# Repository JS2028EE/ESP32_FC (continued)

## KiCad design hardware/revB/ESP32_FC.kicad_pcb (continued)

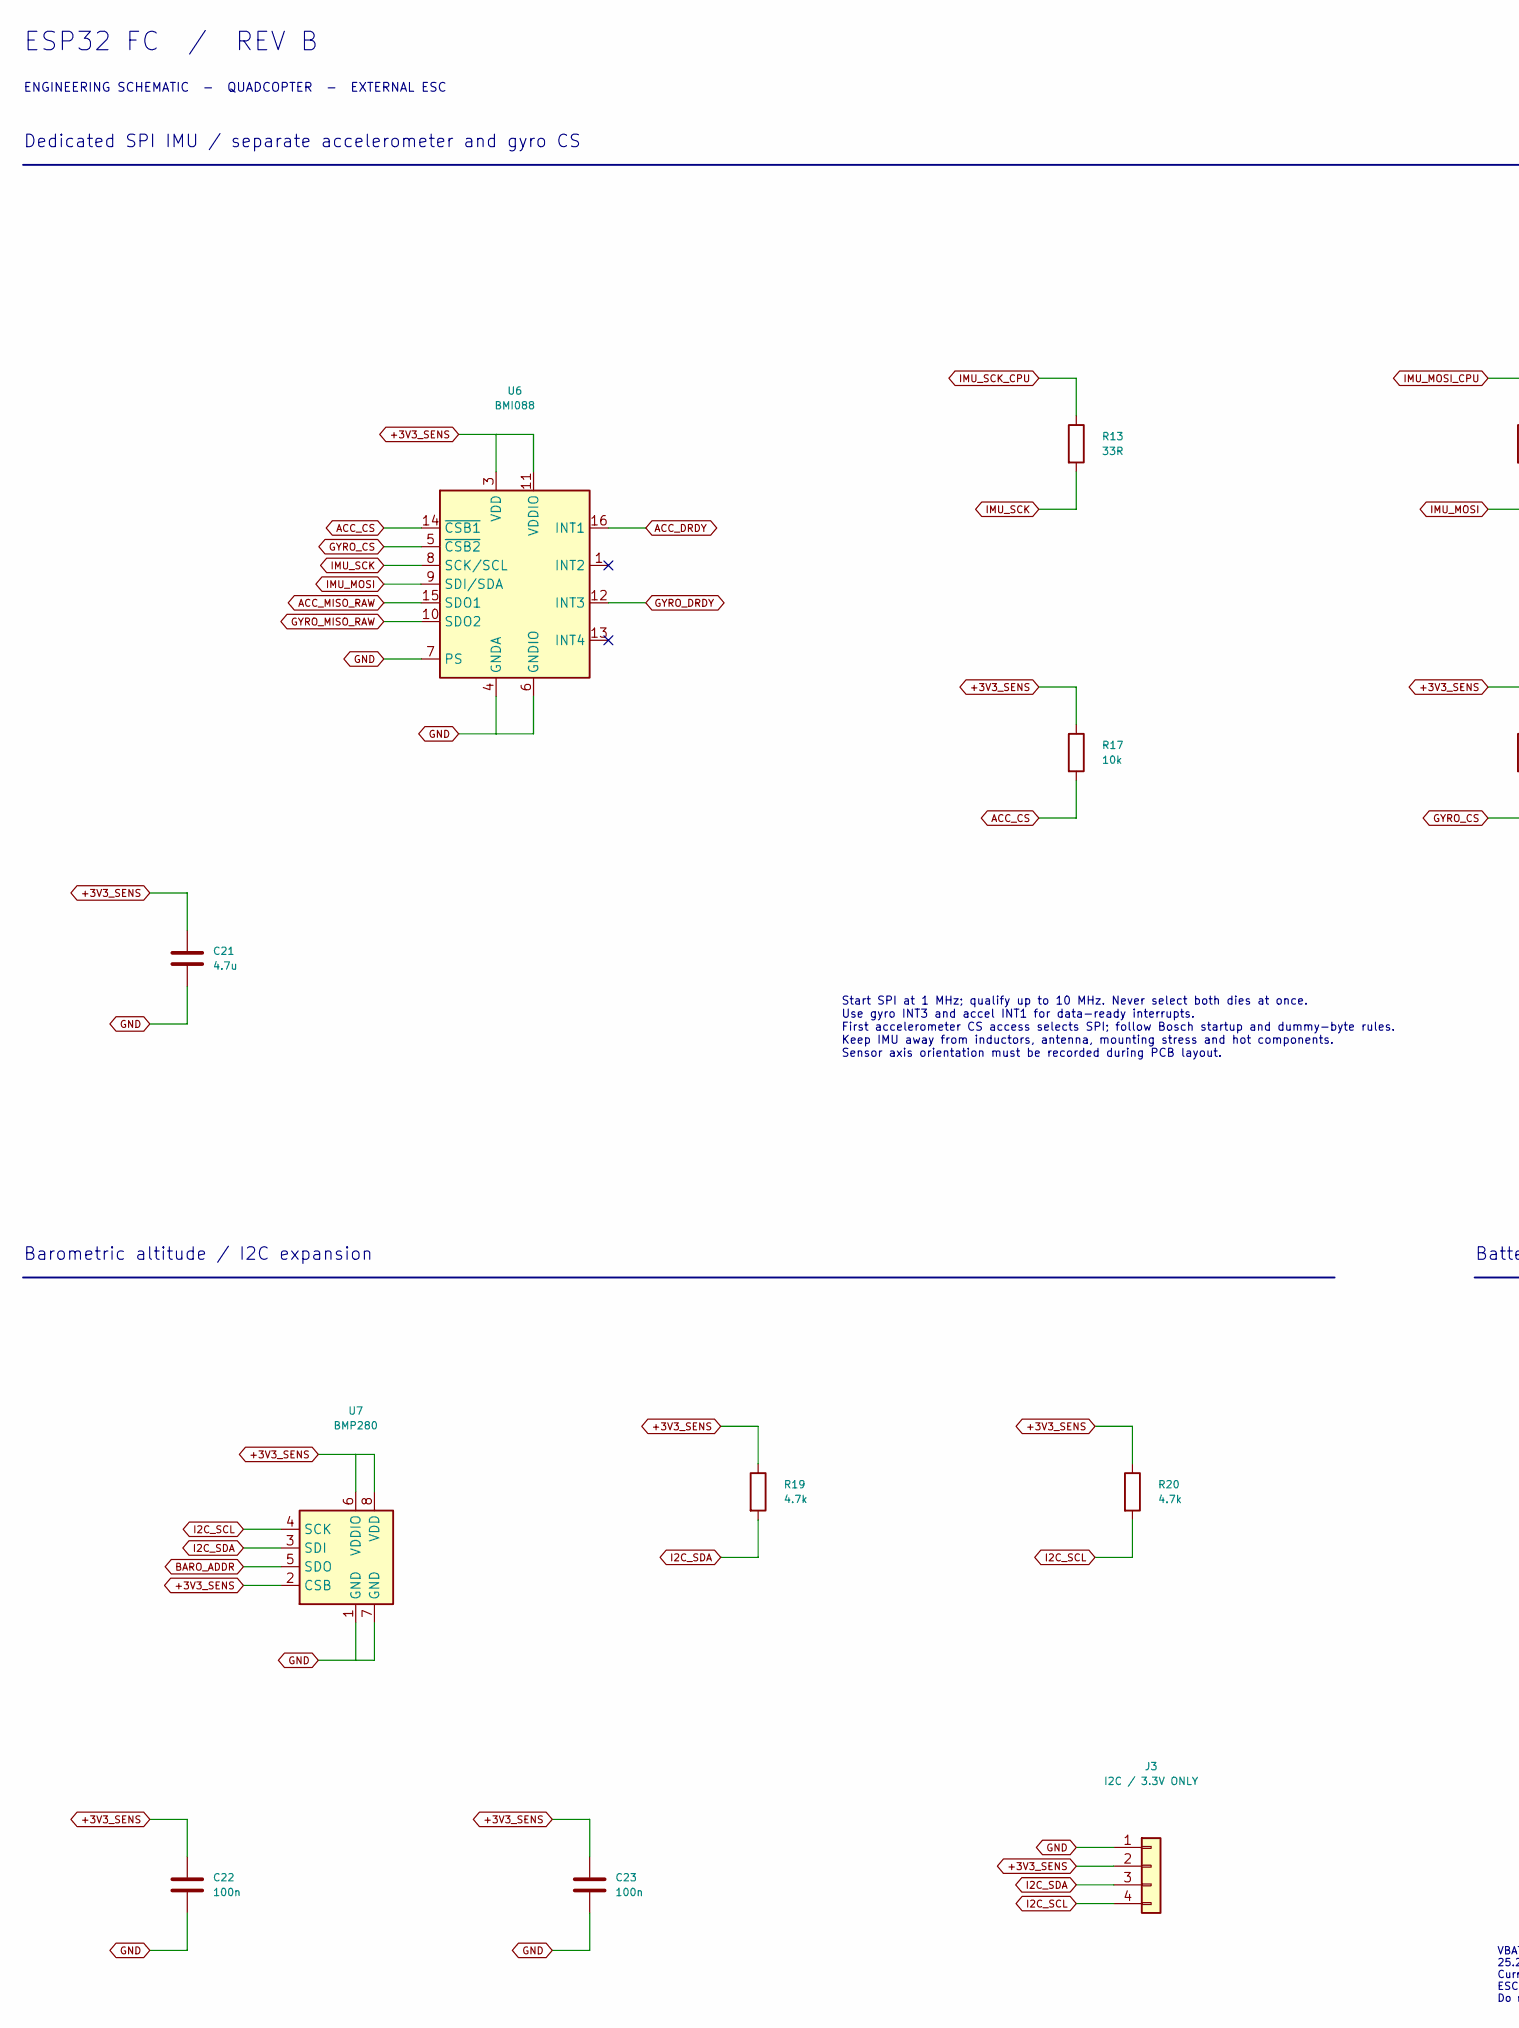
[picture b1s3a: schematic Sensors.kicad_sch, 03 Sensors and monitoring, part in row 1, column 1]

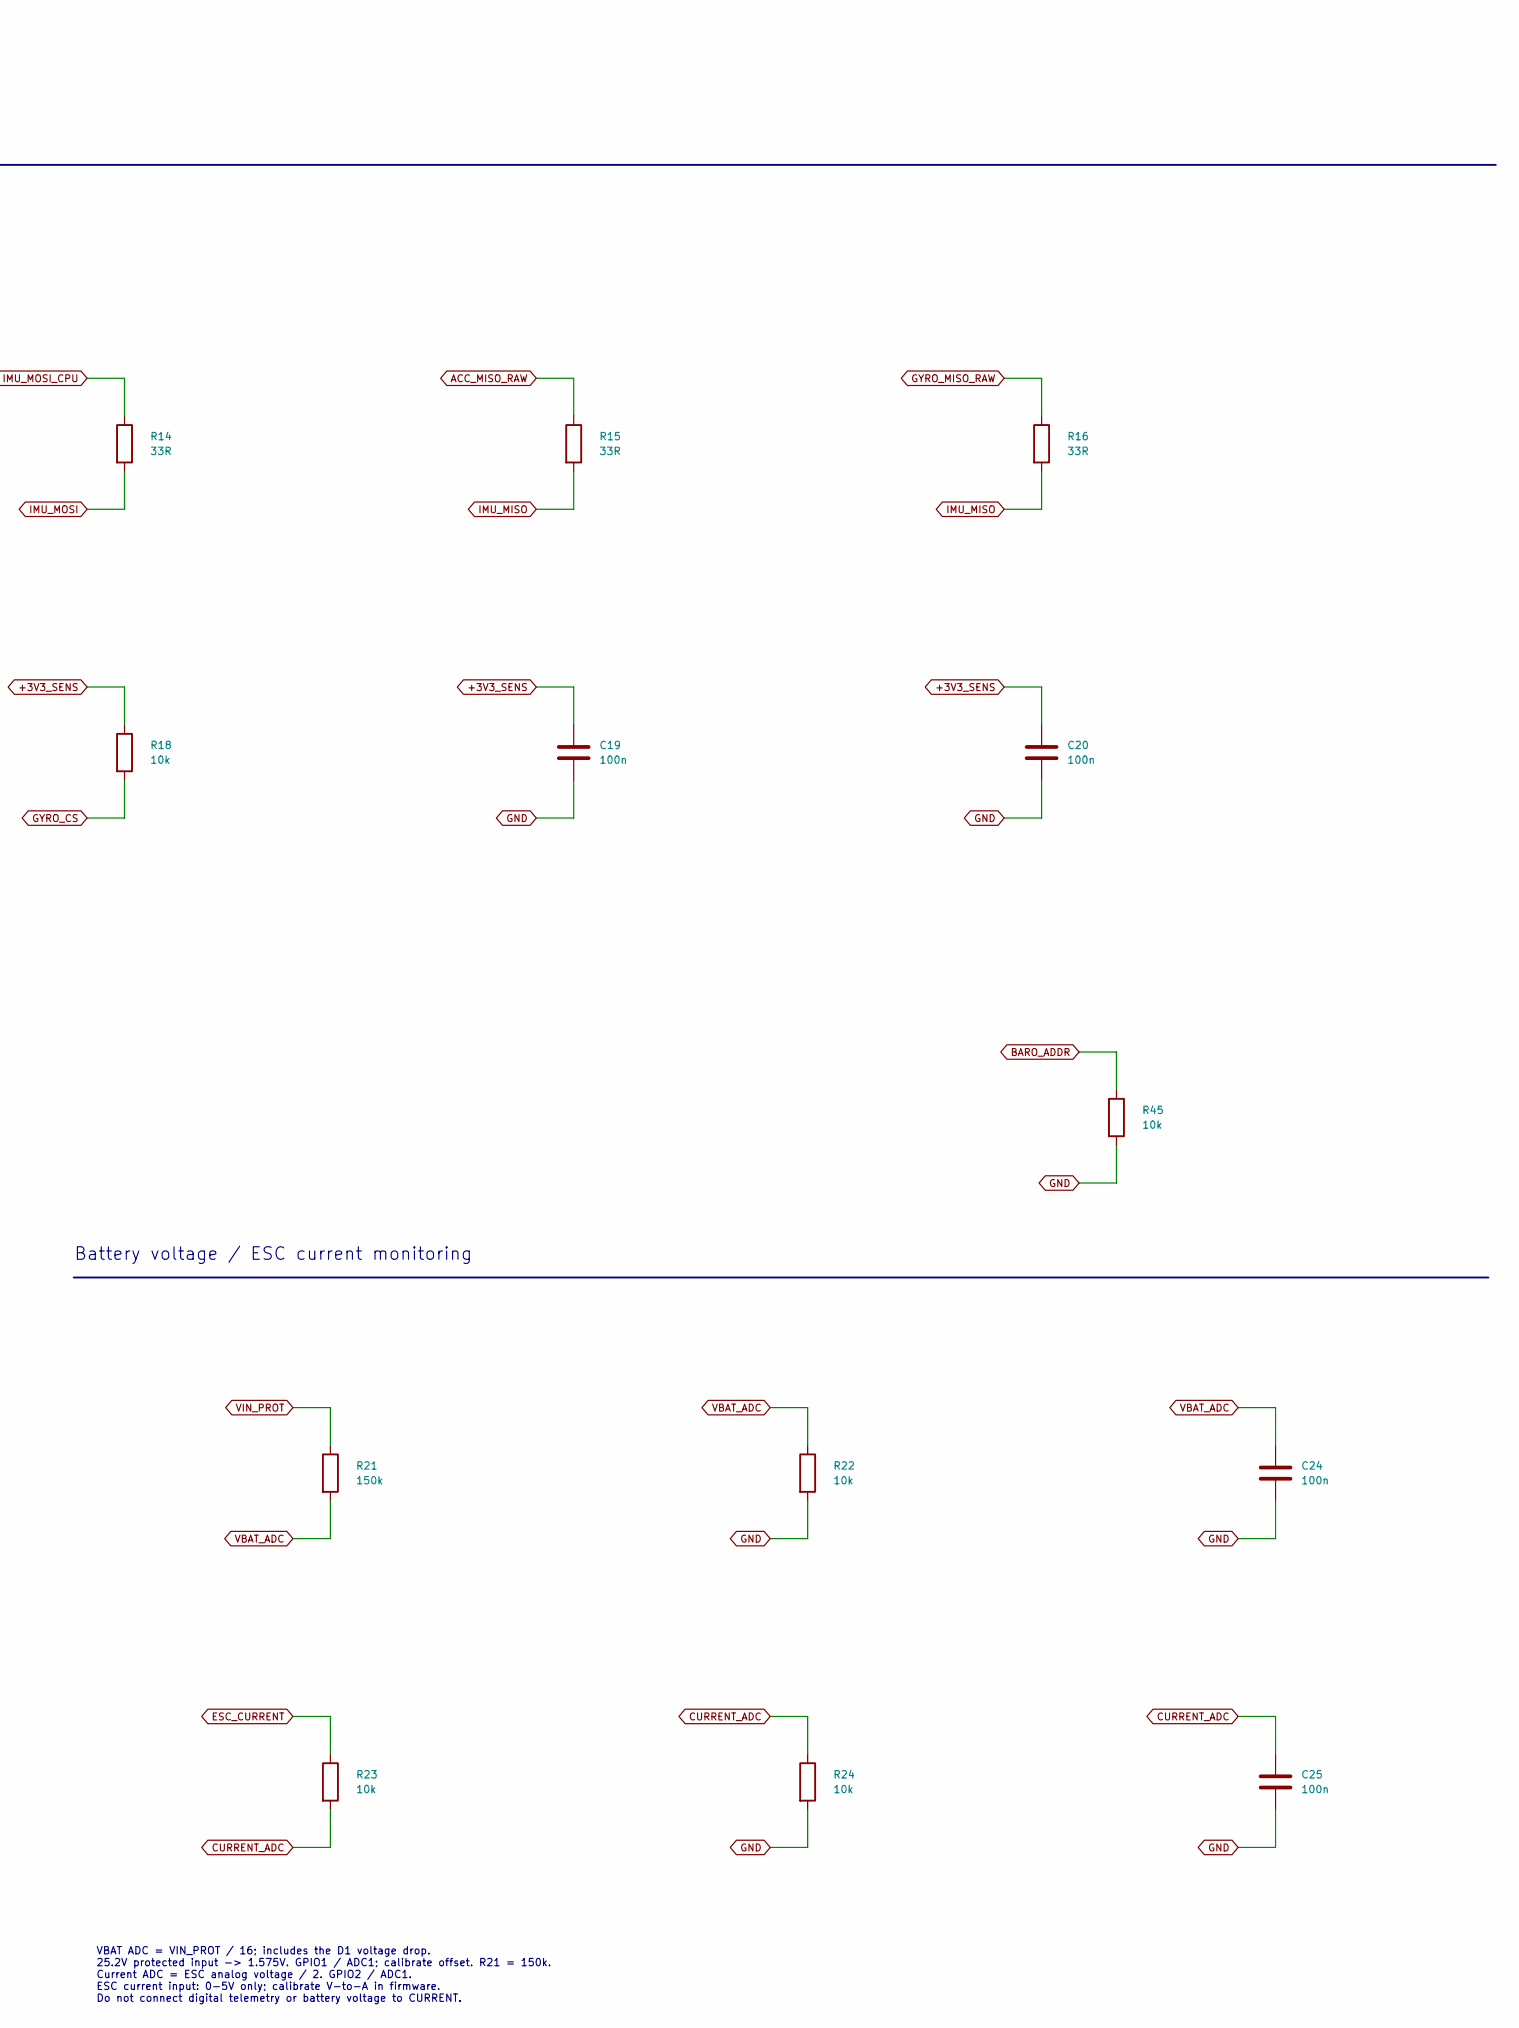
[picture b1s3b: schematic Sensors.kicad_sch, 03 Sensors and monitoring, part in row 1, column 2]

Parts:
C19, C20, C22, C23, C24, C25: 100n; C_0603_1608Metric; MPN GRM188R71C104KA01D
C21: 4.7u; C_0603_1608Metric; MPN GRM188R61C475KE11D
J3: I2C / 3.3V ONLY; PinHeader_1x04_P2.54mm_Vertical; MPN TSW-104-07-G-S
R13, R14, R15, R16: 33R; R_0603_1608Metric; MPN RC0603FR-0733RL
R17, R18, R23, R24, R45: 10k; R_0603_1608Metric; MPN RC0603FR-0710KL
R19, R20: 4.7k; R_0603_1608Metric; MPN RC0603FR-074K7L
R21: 150k; R_0603_1608Metric; MPN RT0603BRD07150KL
R22: 10k; R_0603_1608Metric; MPN RT0603BRD0710KL
U6: BMI088; Bosch_LGA-16_4.5x3mm_P0.5mm_LayoutBorder7x1y_ClockwisePinNu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; MPN BMI088
U7: BMP280; BMP280_SilkClear; MPN BMP280

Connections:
+3V3_SENS: C19.1, C20.1, C21.1, C22.1, C23.1, J3.2, R17.1, R18.1, R19.1, R20.1, U6.3 (VDD), U6.11 (VDDIO), U7.2 (CSB), U7.6 (VDDIO), U7.8 (VDD); also elsewhere on the board
ACC_CS: R17.2, U6.14 (~CSB1); also elsewhere on the board
ACC_DRDY: U6.16 (INT1); also elsewhere on the board
ACC_MISO_RAW: R15.1, U6.15 (SDO1)
BARO_ADDR: R45.1, U7.5 (SDO)
CURRENT_ADC: C25.1, R23.2, R24.1; also elsewhere on the board
ESC_CURRENT: R23.1; also elsewhere on the board
GND: C19.2, C20.2, C21.2, C22.2, C23.2, C24.2, C25.2, J3.1, R22.2, R24.2, R45.2, U6.2 (GNDA), U6.4 (GNDA), U6.6 (GNDIO), U6.7 (PS), U7.1 (GND), U7.7 (GND); also elsewhere on the board
GYRO_CS: R18.2, U6.5 (~CSB2); also elsewhere on the board
GYRO_DRDY: U6.12 (INT3); also elsewhere on the board
GYRO_MISO_RAW: R16.1, U6.10 (SDO2)
I2C_SCL: J3.4, R20.2, U7.4 (SCK); also elsewhere on the board
I2C_SDA: J3.3, R19.2, U7.3 (SDI); also elsewhere on the board
IMU_MISO: R15.2, R16.2; also elsewhere on the board
IMU_MOSI: R14.2, U6.9 (SDI/SDA)
IMU_MOSI_CPU: R14.1; also elsewhere on the board
IMU_SCK: R13.2, U6.8 (SCK/SCL)
IMU_SCK_CPU: R13.1; also elsewhere on the board
VBAT_ADC: C24.1, R21.2, R22.1; also elsewhere on the board
VIN_PROT: R21.1; also elsewhere on the board

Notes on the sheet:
ESP32 FC / REV B
ENGINEERING SCHEMATIC - QUADCOPTER - EXTERNAL ESC
Dedicated SPI IMU / separate accelerometer and gyro CS
Start SPI at 1 MHz; qualify up to 10 MHz. Never select both dies at once. Use gyro INT3 and accel INT1 for data-ready interrupts. First accelerometer CS access selects SPI; follow Bosch startup and dummy-byte rules. Keep IMU away from inductors, antenna, mounting stress and hot components. Sensor a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
Barometric altitude / I2C expansion
Battery voltage / ESC current monitoring
VBAT ADC = VIN_PROT / 16; includes the D1 voltage drop. 25.2V protected input -> 1.575V. GPIO1 / ADC1; calibrate offset. R21 = 150k. Current ADC = ESC analog voltage / 2. GPIO2 / ADC1. ESC current input: 0-5V only; calibrate V-to-A in firmware. Do not connect digital telemetry or battery voltage to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

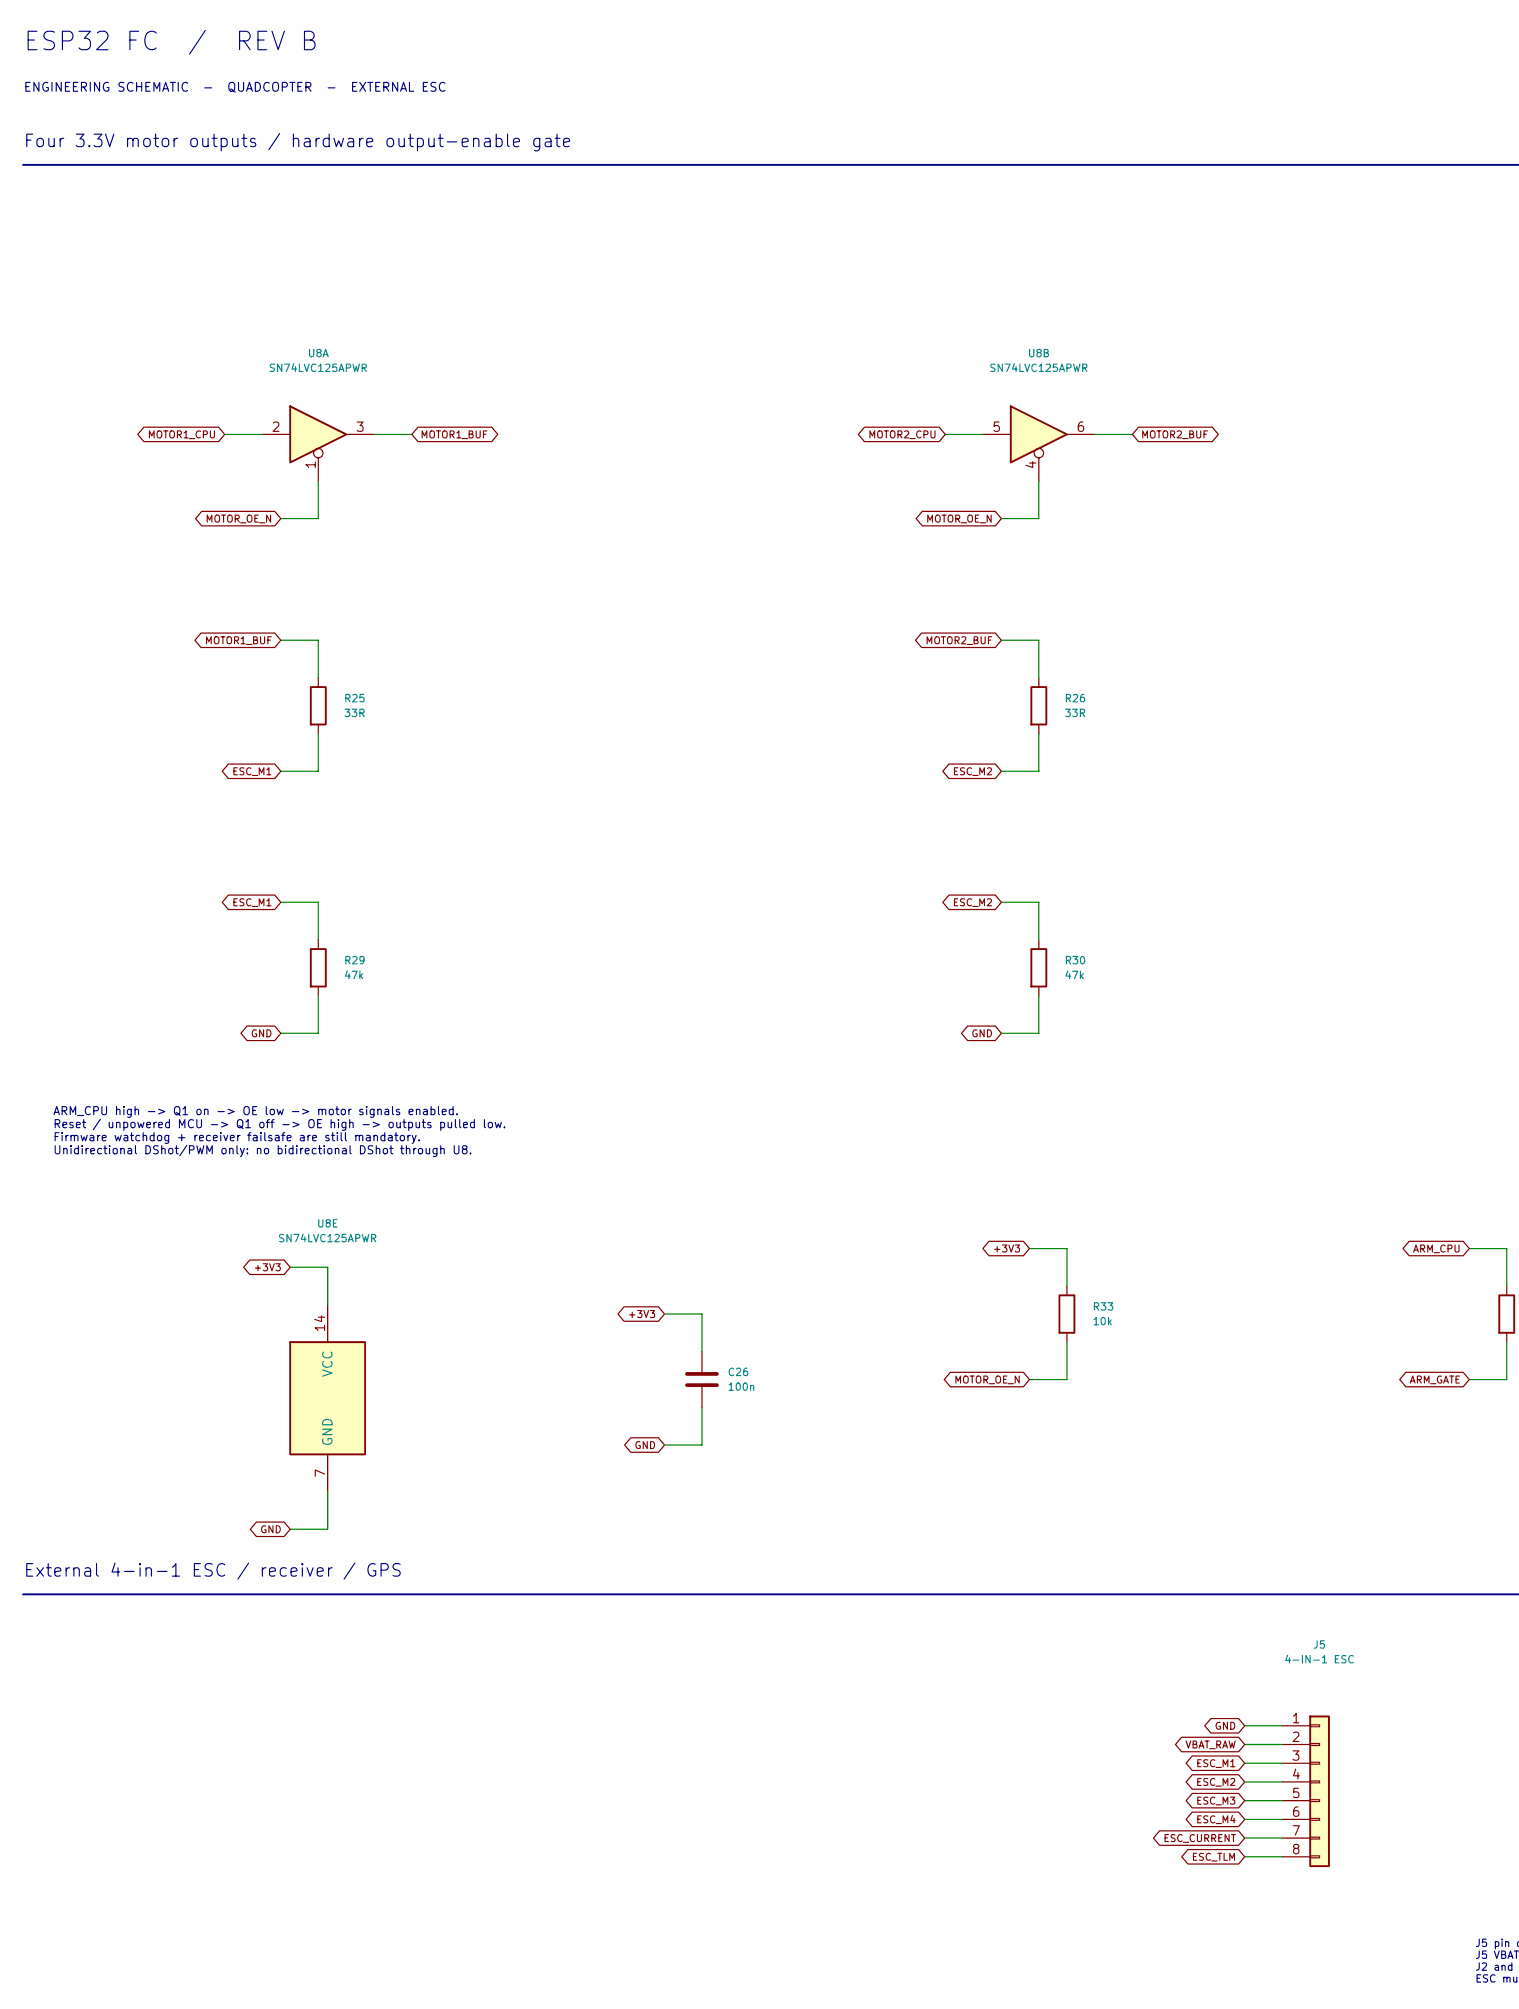
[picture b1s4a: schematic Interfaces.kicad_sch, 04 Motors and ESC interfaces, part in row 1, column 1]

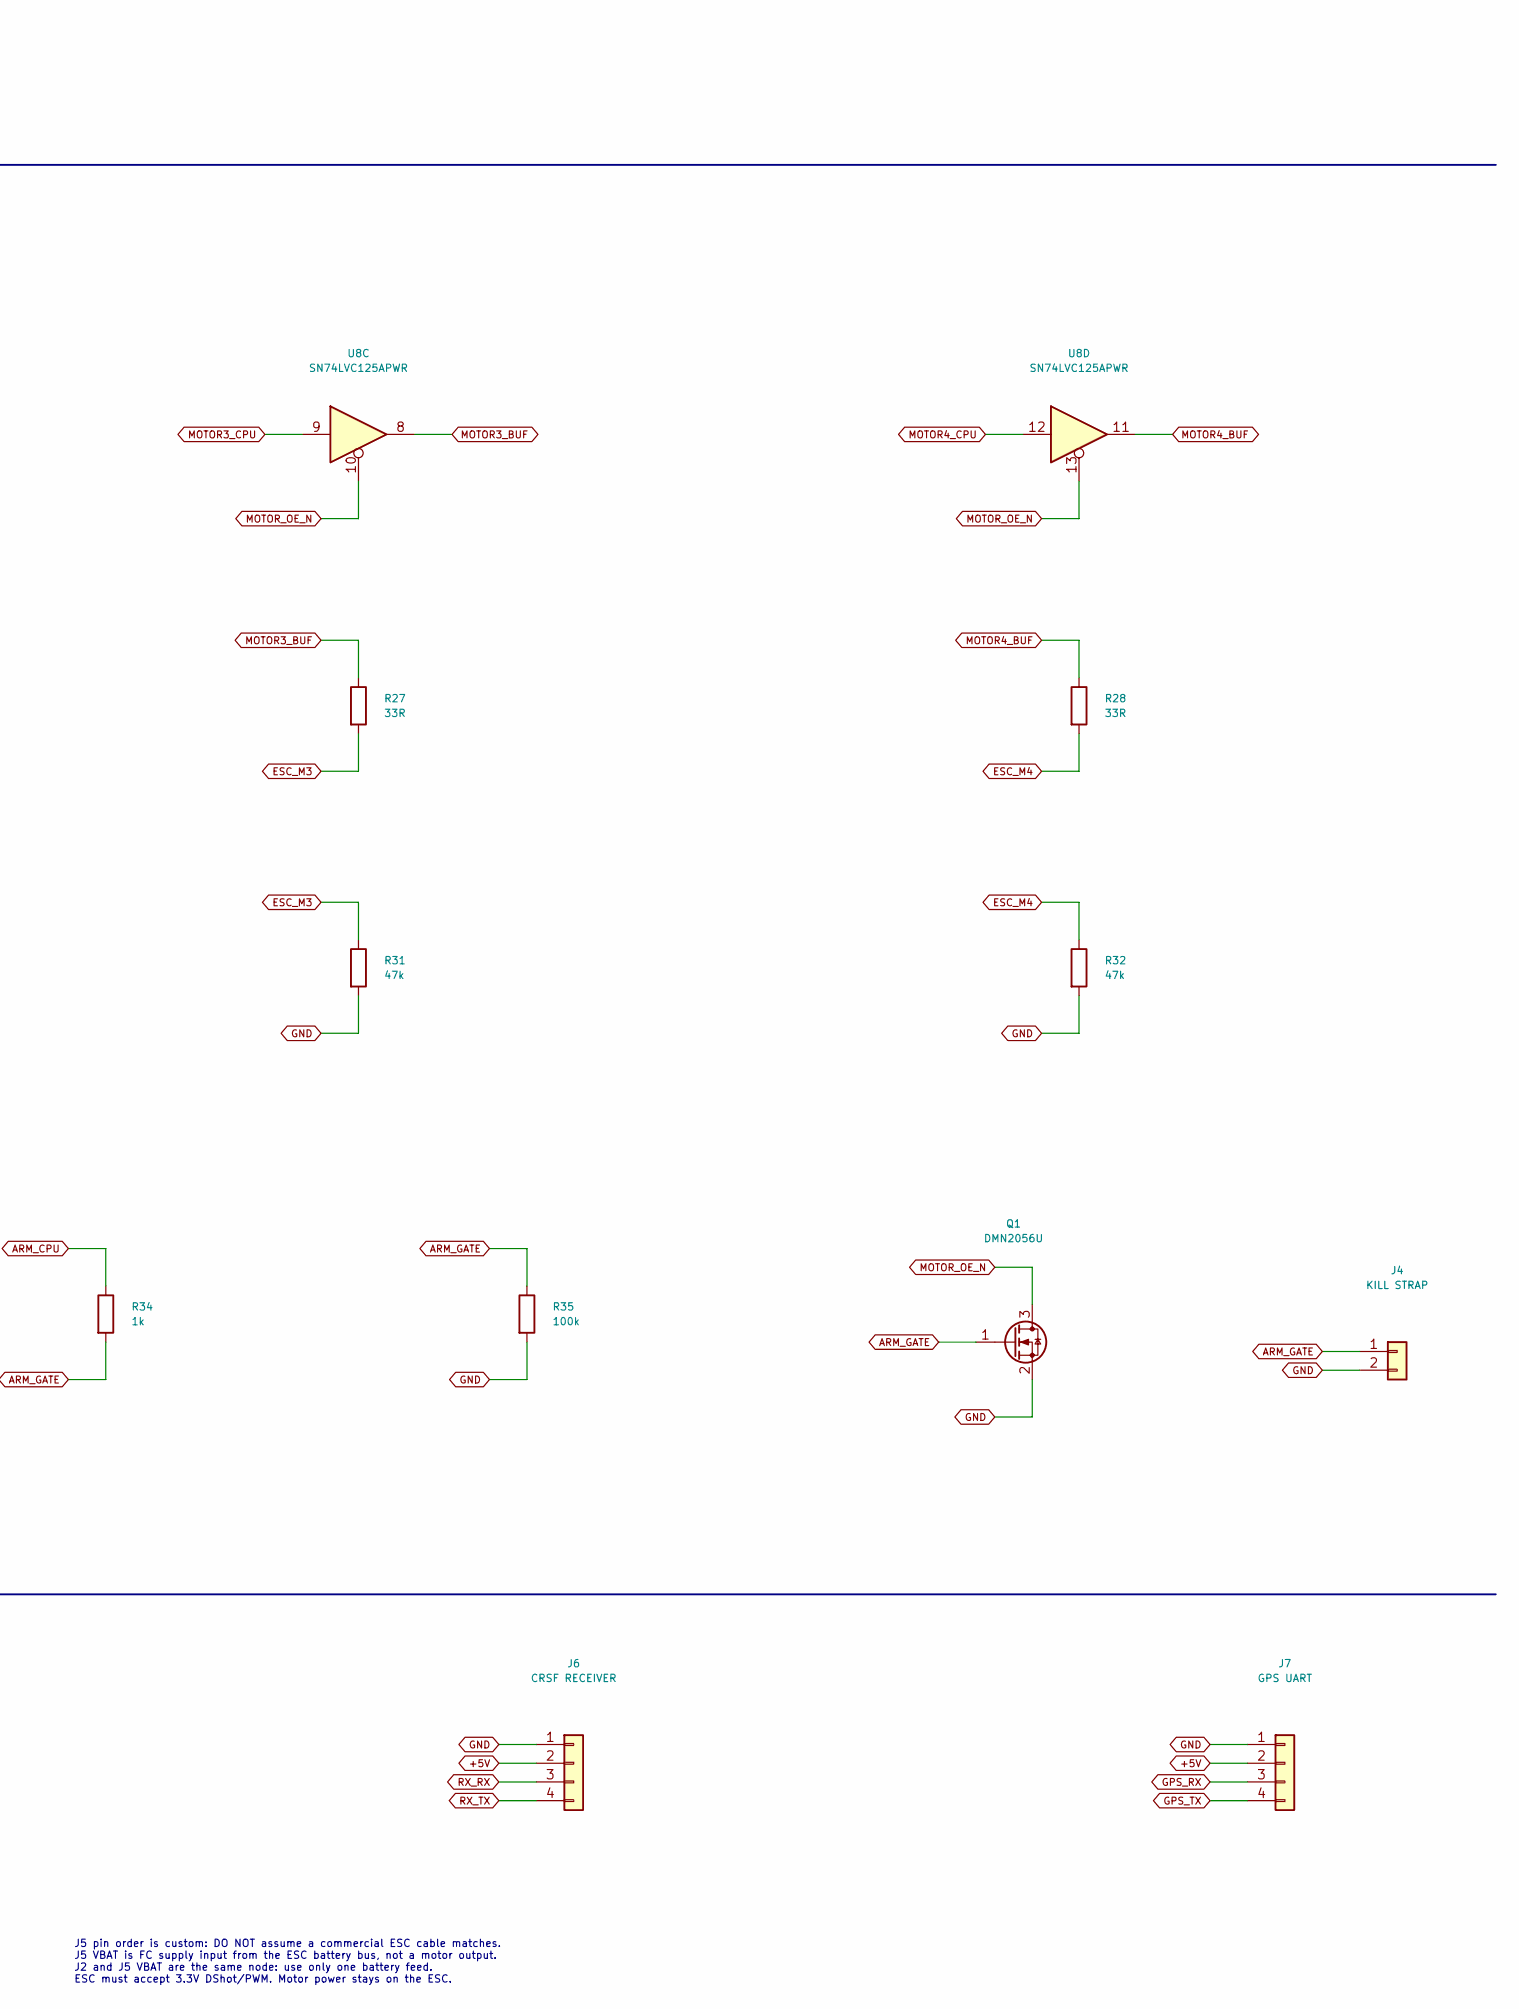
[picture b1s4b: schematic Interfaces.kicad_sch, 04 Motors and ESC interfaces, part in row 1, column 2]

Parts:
C26: 100n; C_0603_1608Metric; MPN GRM188R71C104KA01D
J4: KILL STRAP; PinHeader_1x02_P2.54mm_Vertical; MPN TSW-102-07-G-S
J5: 4-IN-1 ESC; PinHeader_1x08_P2.54mm_Vertical; MPN TSW-108-07-G-S
J6: CRSF RECEIVER; PinHeader_1x04_P2.54mm_Vertical; MPN TSW-104-07-G-S
J7: GPS UART; PinHeader_1x04_P2.54mm_Vertical; MPN TSW-104-07-G-S
Q1: DMN2056U; SOT-23; MPN DMN2056U-7
R25, R26, R27, R28: 33R; R_0603_1608Metric; MPN RC0603FR-0733RL
R29, R30, R31, R32: 47k; R_0603_1608Metric; MPN RC0603FR-0747KL
R33: 10k; R_0603_1608Metric; MPN RC0603FR-0710KL
R34: 1k; R_0603_1608Metric; MPN RC0603FR-071KL
R35: 100k; R_0603_1608Metric; MPN RC0603FR-07100KL
U8: SN74LVC125APWR; TSSOP-14_4.4x5mm_P0.65mm; MPN SN74LVC125APWR

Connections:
+3V3: C26.1, R33.1, U8.14 (VCC); also elsewhere on the board
+5V: J6.2, J7.2; also elsewhere on the board
ARM_CPU: R34.1; also elsewhere on the board
ARM_GATE: J4.1, Q1.1 (G), R34.2, R35.1
ESC_CURRENT: J5.7; also elsewhere on the board
ESC_M1: J5.3, R25.2, R29.1
ESC_M2: J5.4, R26.2, R30.1
ESC_M3: J5.5, R27.2, R31.1
ESC_M4: J5.6, R28.2, R32.1
ESC_TLM: J5.8; also elsewhere on the board
GND: C26.2, J4.2, J5.1, J6.1, J7.1, Q1.2 (S), R29.2, R30.2, R31.2, R32.2, R35.2, U8.7 (GND); also elsewhere on the board
GPS_RX: J7.3; also elsewhere on the board
GPS_TX: J7.4; also elsewhere on the board
MOTOR1_BUF: R25.1, U8.3
MOTOR1_CPU: U8.2; also elsewhere on the board
MOTOR2_BUF: R26.1, U8.6
MOTOR2_CPU: U8.5; also elsewhere on the board
MOTOR3_BUF: R27.1, U8.8
MOTOR3_CPU: U8.9; also elsewhere on the board
MOTOR4_BUF: R28.1, U8.11
MOTOR4_CPU: U8.12; also elsewhere on the board
MOTOR_OE_N: Q1.3 (D), R33.2, U8.1, U8.4, U8.10, U8.13
RX_RX: J6.3; also elsewhere on the board
RX_TX: J6.4; also elsewhere on the board
VBAT_RAW: J5.2; also elsewhere on the board

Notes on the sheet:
ESP32 FC / REV B
ENGINEERING SCHEMATIC - QUADCOPTER - EXTERNAL ESC
Four 3.3V motor outputs / hardware output-enable gate
ARM_CPU high -> Q1 on -> OE low -> motor signals enabled. Reset / unpowered MCU -> Q1 off -> OE high -> outputs pulled low. Firmware watchdog + receiver failsafe are still mandatory. Unidirectional DShot/PWM only: no bidirectional DShot through U8.
External 4-in-1 ESC / receiver / GPS
J5 pin order is custom: DO NOT assume a commercial ESC cable matches. J5 VBAT is FC supply input from the ESC battery bus, not a motor output. J2 and J5 VBAT are the same node: use only one battery feed. ESC must accept 3.3V DShot/PWM. Motor power stays on the ESC.

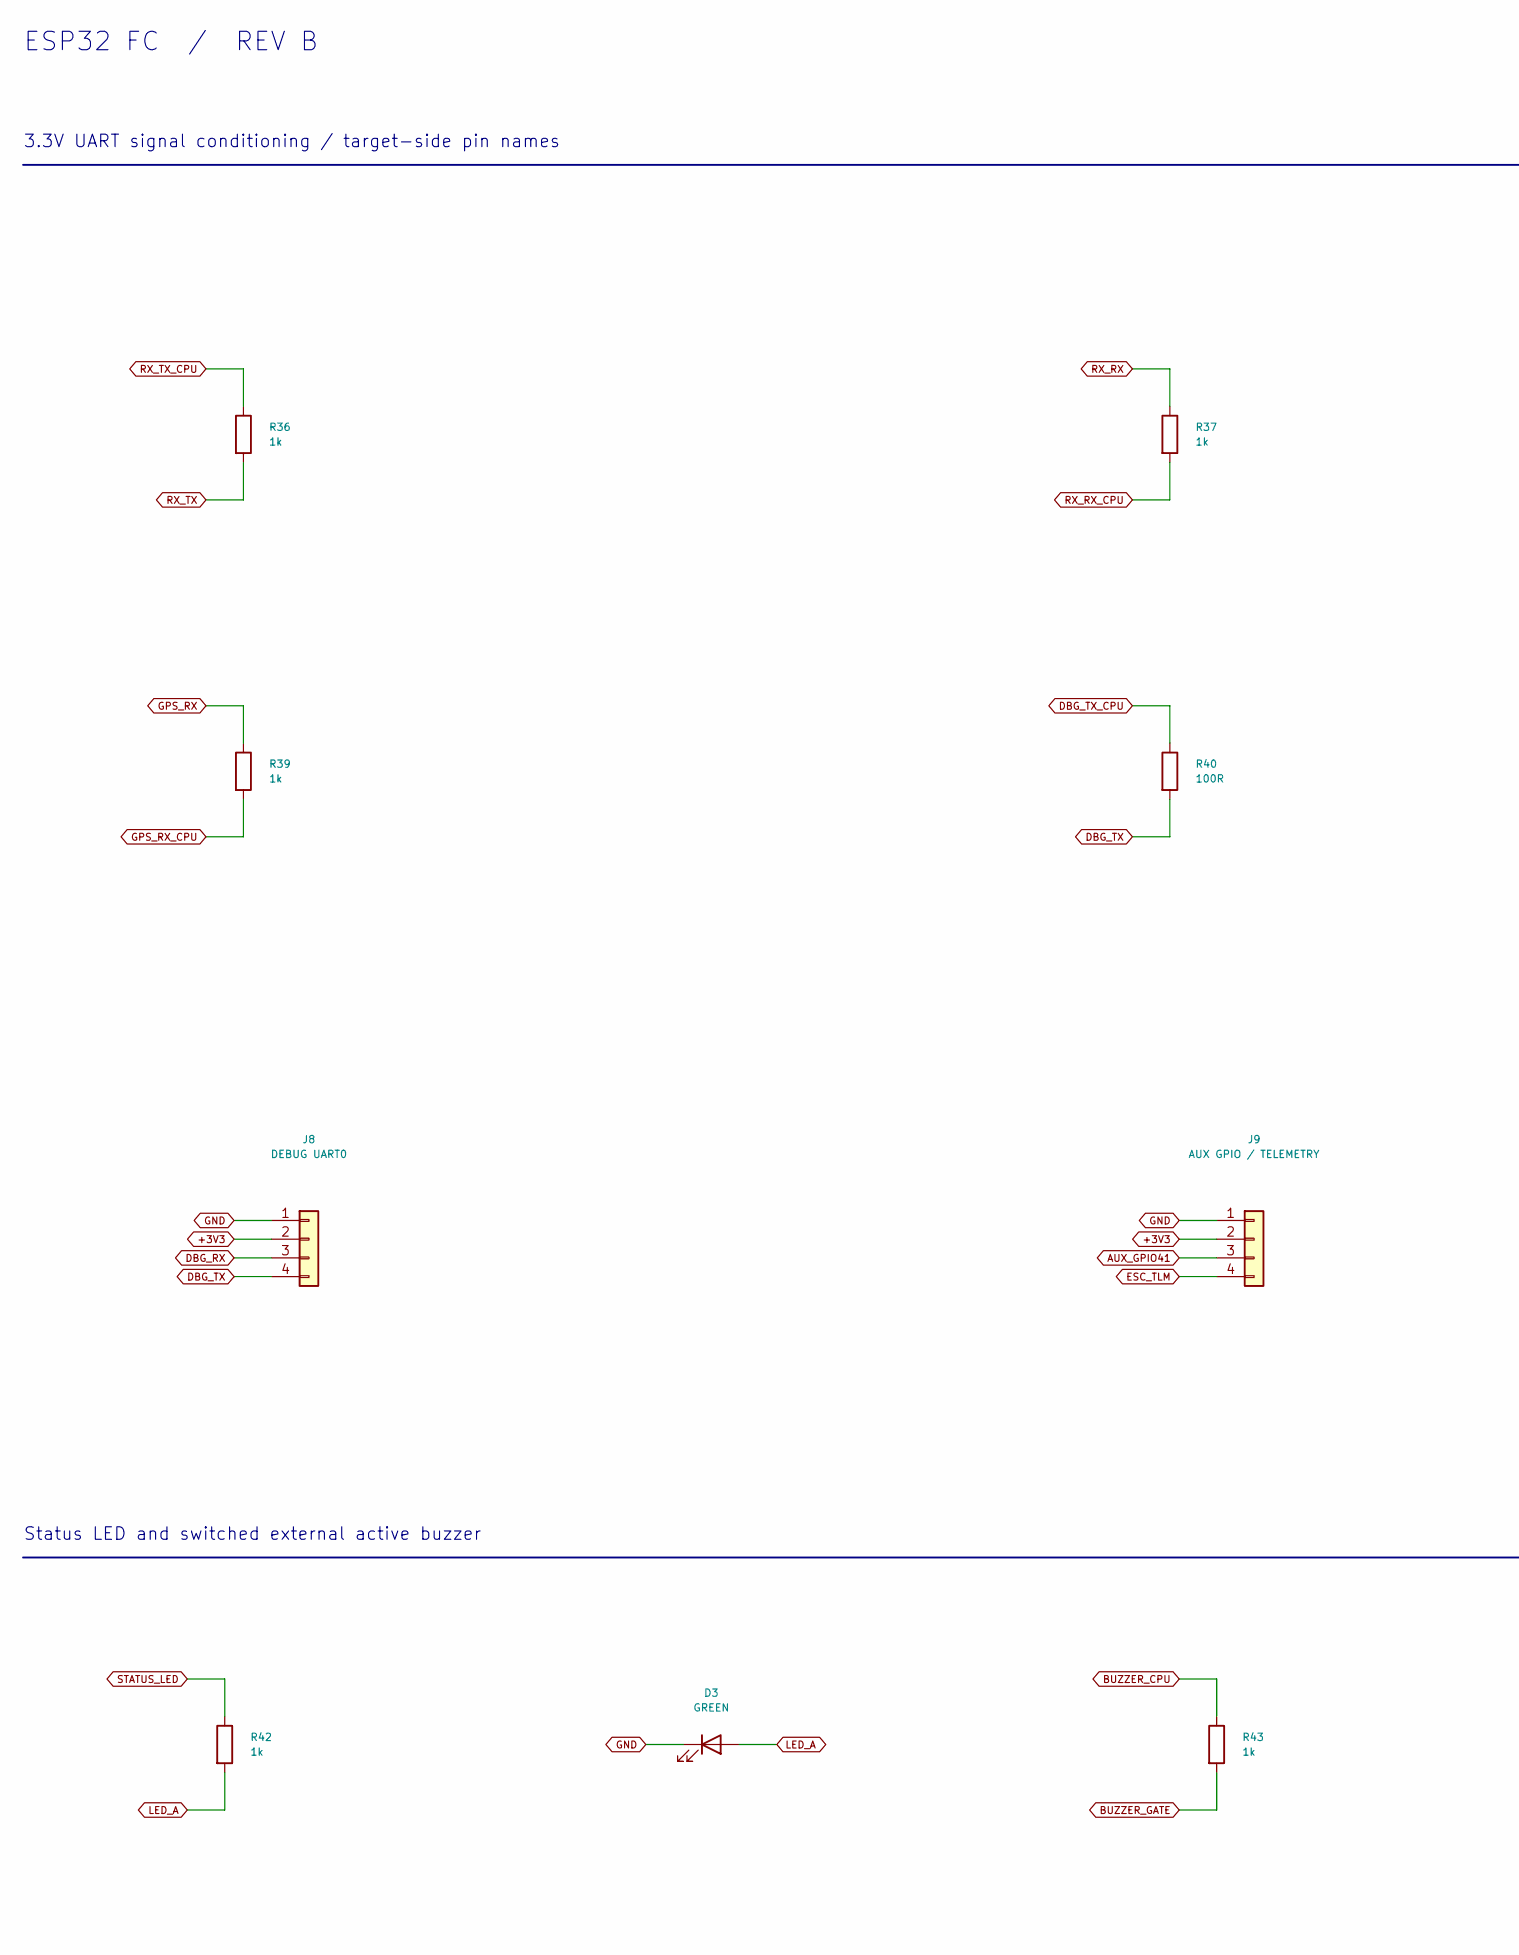
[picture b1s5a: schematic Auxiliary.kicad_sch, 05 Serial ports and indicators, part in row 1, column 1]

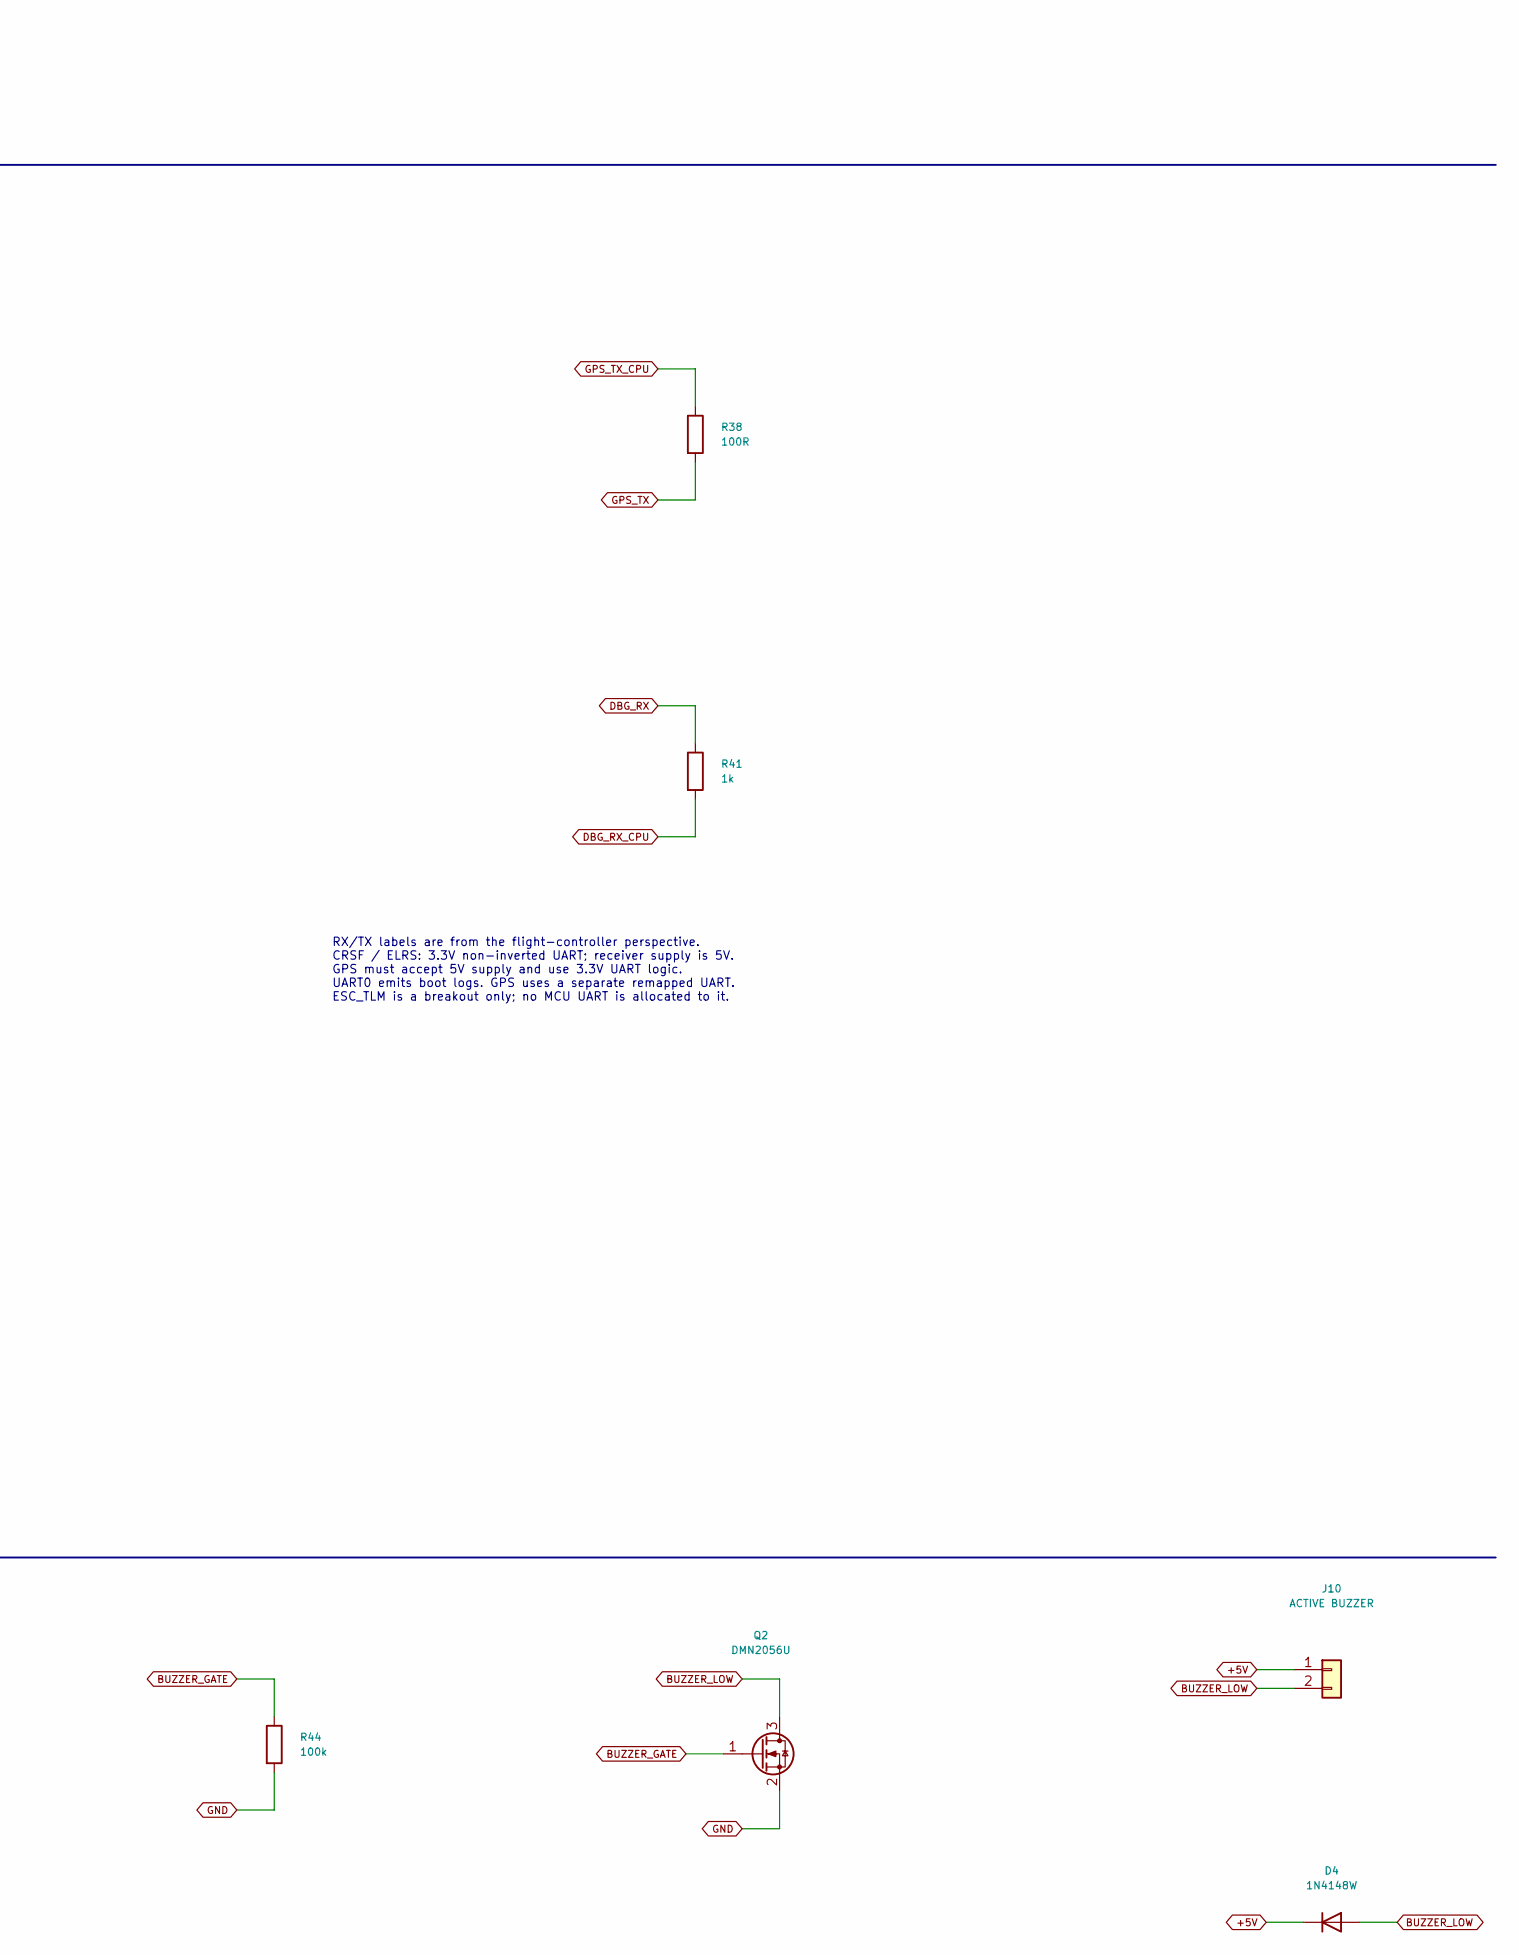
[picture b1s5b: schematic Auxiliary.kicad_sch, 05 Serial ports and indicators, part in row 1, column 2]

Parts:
D3: GREEN; LED_0603_1608Metric; MPN APT1608LZGCK
D4: 1N4148W; D_SOD-123; MPN 1N4148W-7-F
J8: DEBUG UART0; PinHeader_1x04_P2.54mm_Vertical; MPN TSW-104-07-G-S
J9: AUX GPIO / TELEMETRY; PinHeader_1x04_P2.54mm_Vertical; MPN TSW-104-07-G-S
J10: ACTIVE BUZZER; PinHeader_1x02_P2.54mm_Vertical; MPN TSW-102-07-G-S
Q2: DMN2056U; SOT-23; MPN DMN2056U-7
R36, R37, R39, R41, R42, R43: 1k; R_0603_1608Metric; MPN RC0603FR-071KL
R38, R40: 100R; R_0603_1608Metric; MPN RC0603FR-07100RL
R44: 100k; R_0603_1608Metric; MPN RC0603FR-07100KL

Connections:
+3V3: J8.2, J9.2; also elsewhere on the board
+5V: D4.1 (K), J10.1; also elsewhere on the board
AUX_GPIO41: J9.3; also elsewhere on the board
BUZZER_CPU: R43.1; also elsewhere on the board
BUZZER_GATE: Q2.1 (G), R43.2, R44.1
BUZZER_LOW: D4.2 (A), J10.2, Q2.3 (D)
DBG_RX: J8.3, R41.1
DBG_RX_CPU: R41.2; also elsewhere on the board
DBG_TX: J8.4, R40.2
DBG_TX_CPU: R40.1; also elsewhere on the board
ESC_TLM: J9.4; also elsewhere on the board
GND: D3.1 (K), J8.1, J9.1, Q2.2 (S), R44.2; also elsewhere on the board
GPS_RX: R39.1; also elsewhere on the board
GPS_RX_CPU: R39.2; also elsewhere on the board
GPS_TX: R38.2; also elsewhere on the board
GPS_TX_CPU: R38.1; also elsewhere on the board
LED_A: D3.2 (A), R42.2
RX_RX: R37.1; also elsewhere on the board
RX_RX_CPU: R37.2; also elsewhere on the board
RX_TX: R36.2; also elsewhere on the board
RX_TX_CPU: R36.1; also elsewhere on the board
STATUS_LED: R42.1; also elsewhere on the board

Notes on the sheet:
ESP32 FC / REV B
3.3V UART signal conditioning / target-side pin names
RX/TX labels are from the flight-controller perspective. CRSF / ELRS: 3.3V non-inverted UART; receiver supply is 5V. GPS must accept 5V supply and use 3.3V UART logic. UART0 emits boot logs. GPS uses a separate remapped UART. ESC_TLM is a breakout only; no MCU UART is allocated to it.
Status LED and switched external active buzzer
